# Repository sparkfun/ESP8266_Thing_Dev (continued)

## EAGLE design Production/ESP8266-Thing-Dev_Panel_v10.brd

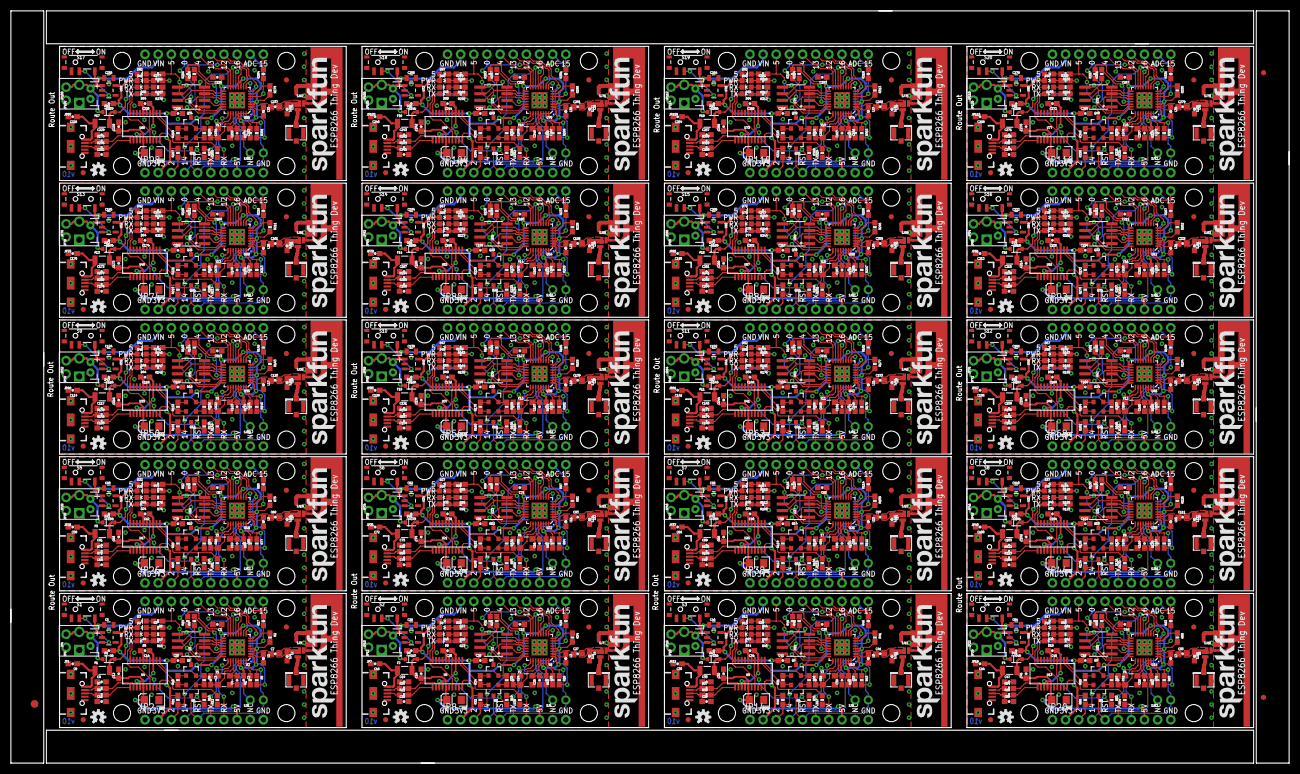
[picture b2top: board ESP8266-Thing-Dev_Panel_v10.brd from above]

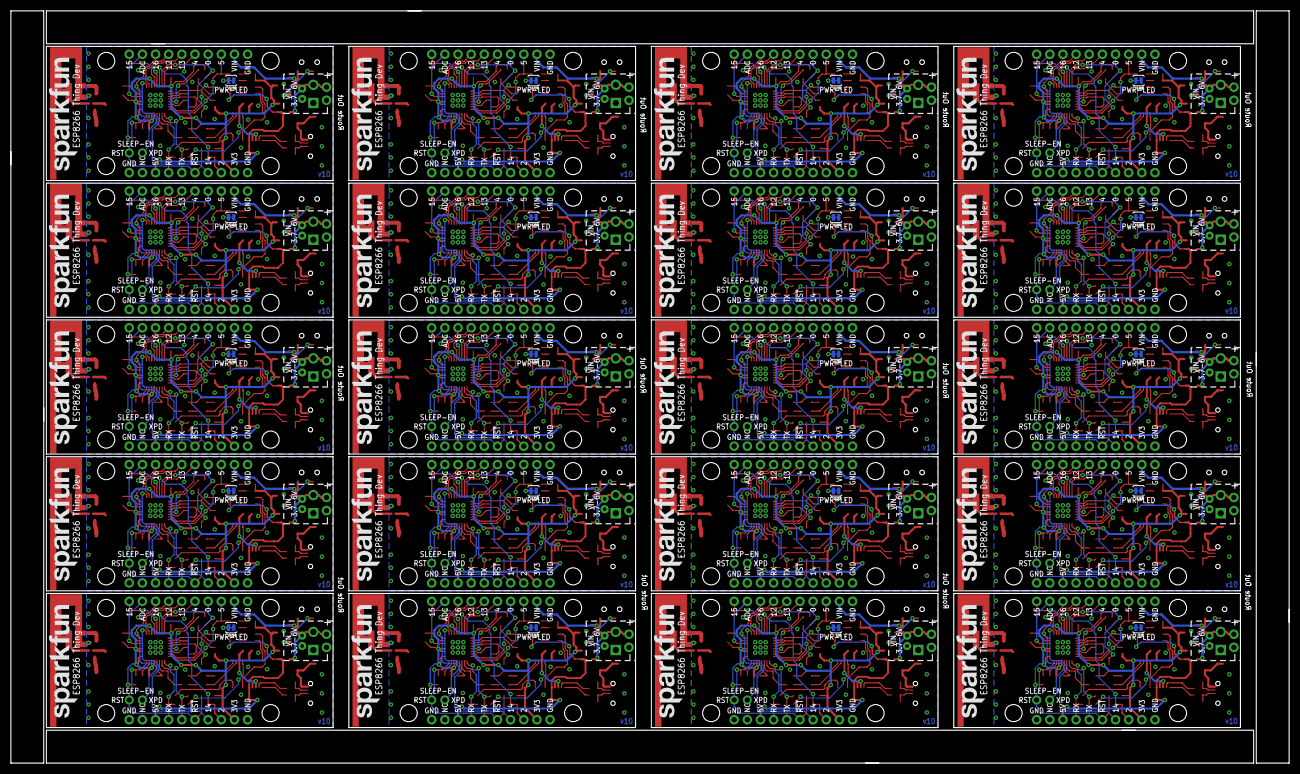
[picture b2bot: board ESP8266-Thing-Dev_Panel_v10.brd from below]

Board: 2 copper layers, 246.9 x 145.3 mm, 1363 parts (40 on the bottom side), 1040 nets.

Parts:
C1, C15, C29, C43, C57, C71, C85, C99, C113, C127, C141, C155, C169, C183, C197, C211, C225, C239, C253, C267: 10uF; 0603-CAP
C2, C8, C10, C12, C14, C16, C18, C20, C23, C28, C30, C32, C34, C37, C42, C44, C46, C48, C51, C56, C58, C60, C62, C65, C70, C72, C74, C76, C79, C84, C86, C88, C90, C93, C98, C100, C102, C104, C107, C112, C114, C116, C118, C121, C126, C128, C130, C132, C135, C140, C142, C144, C146, C149, C154, C156, C158, C160, C163, C168, C170, C172, C174, C177, C182, C184, C186, C188, C191, C196, C198, C200, C202, C205, C210, C212, C214, C216, C219, C224, C226, C228, C230, C233, C238, C240, C242, C244, C247, C252, C254, C256, C258, C261, C266, C268, C270, C272, C275, C280: 0.1uF; 0603-CAP
C3, C4, C24, C25, C38, C39, C52, C53, C66, C67, C80, C81, C94, C95, C108, C109, C122, C123, C136, C137, C150, C151, C164, C165, C178, C179, C192, C193, C206, C207, C220, C221, C234, C235, C248, C249, C262, C263, C276, C277: 10pF; 0603-CAP
C5, C26, C40, C54, C68, C82, C96, C110, C124, C138, C152, C166, C180, C194, C208, C222, C236, C250, C264, C278: 1.0uF; 0805
C6, C17, C31, C45, C59, C73, C87, C101, C115, C129, C143, C157, C171, C185, C199, C213, C227, C241, C255, C269: 2.2uF; 0603-CAP
C7, C27, C41, C55, C69, C83, C97, C111, C125, C139, C153, C167, C181, C195, C209, C223, C237, C251, C265, C279: 5.6pF; 0603-CAP
C9, C11, C19, C22, C33, C36, C47, C50, C61, C64, C75, C78, C89, C92, C103, C106, C117, C120, C131, C134, C145, C148, C159, C162, C173, C176, C187, C190, C201, C204, C215, C218, C229, C232, C243, C246, C257, C260, C271, C274: 47pF; 0603-CAP
C13, C21, C35, C49, C63, C77, C91, C105, C119, C133, C147, C161, C175, C189, C203, C217, C231, C245, C259, C273: 10uF; EIA3216
D1, D8, D13, D18, D23, D28, D33, D38, D43, D48, D53, D58, D63, D68, D73, D78, D83, D88, D93, D98: BAT20J; SOD-323
D2, D6, D11, D16, D21, D26, D31, D36, D41, D46, D51, D56, D61, D66, D71, D76, D81, D86, D91, D96: RED; LED-0603
D3, D7, D12, D17, D22, D27, D32, D37, D42, D47, D52, D57, D62, D67, D72, D77, D82, D87, D92, D97: BLUE; LED-0603
D4, D10, D15, D20, D25, D30, D35, D40, D45, D50, D55, D60, D65, D70, D75, D80, D85, D90, D95, D100: Yellow; LED-0603
D5, D9, D14, D19, D24, D29, D34, D39, D44, D49, D54, D59, D64, D69, D74, D79, D84, D89, D94, D99: GREEN; LED-0603
E1, E2, E3, E4, E5, E6, E7, E8, E9, E10, E11, E12, E13, E14, E15, E16, E17, E18, E19, E20: ANTENNATRACE; TRACE_ANTENNA_2.4GHZ_25.7MM
E$1: FIDUCIAL-1.5X3
E$7, E$8: FIDUCIAL-1X2
F1, F2, F3, F4, F5, F6, F7, F8, F9, F10, F11, F12, F13, F14, F15, F16, F17, F18, F19, F20: 500mA; PTC-1206
FID1, FID2, FID3, FID4, FID5, FID6, FID7, FID8, FID9, FID10, FID11, FID12, FID13, FID14, FID15, FID16, FID17, FID18, FID19, FID20, FID21, FID22, FID23, FID24, FID25, FID26, FID27, FID28, FID29, FID30, FID31, FID32, FID33, FID34, FID35, FID36, FID37, FID38, FID39, FID40: FIDUCIAL1X2; FIDUCIAL-1X2
J1, J2, J3, J4, J5, J6, J7, J8, J9, J10, J11, J12, J13, J14, J15, J16, J17, J18, J19, J20: DNP; U.FL
JP1, JP7, JP13, JP19, JP25, JP31, JP37, JP43, JP49, JP55, JP61, JP67, JP73, JP79, JP85, JP91, JP97, JP103, JP109, JP115: USB-B-MICRO-SMD_V03
JP2, JP3, JP8, JP9, JP14, JP15, JP20, JP21, JP26, JP27, JP32, JP33, JP38, JP39, JP44, JP45, JP50, JP51, JP56, JP57, JP62, JP63, JP68, JP69, JP74, JP75, JP80, JP81, JP86, JP87, JP92, JP93, JP98, JP99, JP104, JP105, JP110, JP111, JP116, JP117: 1X10_NO_SILK
JP4, JP10, JP16, JP22, JP28, JP34, JP40, JP46, JP52, JP58, JP64, JP70, JP76, JP82, JP88, JP94, JP100, JP106, JP112, JP118: JST-2-PTH
JP5, JP11, JP17, JP23, JP29, JP35, JP41, JP47, JP53, JP59, JP65, JP71, JP77, JP83, JP89, JP95, JP101, JP107, JP113, JP119: 1X02_NO_SILK
JP6, JP12, JP18, JP24, JP30, JP36, JP42, JP48, JP54, JP60, JP66, JP72, JP78, JP84, JP90, JP96, JP102, JP108, JP114, JP120: SCREWTERMINAL-3.5MM-2-NS
L1, L2, L3, L4, L5, L6, L7, L8, L9, L10, L11, L12, L13, L14, L15, L16, L17, L18, L19, L20, L21, L22, L23, L24, L25, L26, L27, L28, L29, L30, L31, L32, L33, L34, L35, L36, L37, L38, L39, L40: DNP; 0603
LOGO1, LOGO3, LOGO4, LOGO6, LOGO7, LOGO9, LOGO10, LOGO12, LOGO13, LOGO15, LOGO16, LOGO18, LOGO19, LOGO21, LOGO22, LOGO24, LOGO25, LOGO27, LOGO28, LOGO30, LOGO31, LOGO33, LOGO34, LOGO36, LOGO37, LOGO39, LOGO40, LOGO42, LOGO43, LOGO45, LOGO46, LOGO48, LOGO49, LOGO51, LOGO52, LOGO54, LOGO55, LOGO57, LOGO58, LOGO60: SFE_LOGO_NAME.2_INCH; SFE_LOGO_NAME_.2
LOGO2, LOGO5, LOGO8, LOGO11, LOGO14, LOGO17, LOGO20, LOGO23, LOGO26, LOGO29, LOGO32, LOGO35, LOGO38, LOGO41, LOGO44, LOGO47, LOGO50, LOGO53, LOGO56, LOGO59: OSHW-LOGOS; OSHW-LOGO-S
Q1, Q2, Q3, Q4, Q5, Q6, Q7, Q8, Q9, Q10, Q11, Q12, Q13, Q14, Q15, Q16, Q17, Q18, Q19, Q20, Q21, Q22, Q23, Q24, Q25, Q26, Q27, Q28, Q29, Q30, Q31, Q32, Q33, Q34, Q35, Q36, Q37, Q38, Q39, Q40: MMBT2222A; SOT23-3
R1, R18, R35, R52, R69, R86, R103, R120, R137, R154, R171, R188, R205, R222, R239, R256, R273, R290, R307, R324: 12k; 0603-RES
R2, R5, R9, R10, R11, R14, R17, R24, R26, R29, R31, R32, R33, R34, R41, R43, R46, R48, R49, R50, R51, R58, R60, R63, R65, R66, R67, R68, R75, R77, R80, R82, R83, R84, R85, R92, R94, R97, R99, R100, R101, R102, R109, R111, R114, R116, R117, R118, R119, R126, R128, R131, R133, R134, R135, R136, R143, R145, R148, R150, R151, R152, R153, R160, R162, R165, R167, R168, R169, R170, R177, R179, R182, R184, R185, R186, R187, R194, R196, R199, R201, R202, R203, R204, R211, R213, R216, R218, R219, R220, R221, R228, R230, R233, R235, R236, R237, R238, R245, R247, R250, R252, R253, R254, R255, R262, R264, R267, R269, R270, R271, R272, R279, R281, R284, R286, R287, R288, R289, R296, R298, R301, R303, R304, R305, R306, R313, R315, R318, R320, R321, R322, R323, R330, R332, R335, R337, R338, R339, R340: 10K; 0603-RES
R3, R4, R6, R22, R25, R27, R39, R42, R44, R56, R59, R61, R73, R76, R78, R90, R93, R95, R107, R110, R112, R124, R127, R129, R141, R144, R146, R158, R161, R163, R175, R178, R180, R192, R195, R197, R209, R212, R214, R226, R229, R231, R243, R246, R248, R260, R263, R265, R277, R280, R282, R294, R297, R299, R311, R314, R316, R328, R331, R333: 200; 0603-RES
R7, R8, R20, R21, R37, R38, R54, R55, R71, R72, R88, R89, R105, R106, R122, R123, R139, R140, R156, R157, R173, R174, R190, R191, R207, R208, R224, R225, R241, R242, R258, R259, R275, R276, R292, R293, R309, R310, R326, R327: 27; 0603-RES
R12, R13, R15, R16, R19, R23, R28, R30, R36, R40, R45, R47, R53, R57, R62, R64, R70, R74, R79, R81, R87, R91, R96, R98, R104, R108, R113, R115, R121, R125, R130, R132, R138, R142, R147, R149, R155, R159, R164, R166, R172, R176, R181, R183, R189, R193, R198, R200, R206, R210, R215, R217, R223, R227, R232, R234, R240, R244, R249, R251, R257, R261, R266, R268, R274, R278, R283, R285, R291, R295, R300, R302, R308, R312, R317, R319, R325, R329, R334, R336: 1K; 0603-RES
S1, S2, S3, S4, S5, S6, S7, S8, S9, S10, S11, S12, S13, S14, S15, S16, S17, S18, S19, S20: SWITCH-SPST-SMD-A
SJ1, SJ6, SJ10, SJ14, SJ18, SJ22, SJ26, SJ30, SJ34, SJ38, SJ42, SJ46, SJ50, SJ54, SJ58, SJ62, SJ66, SJ70, SJ74, SJ78: PWRLED; PAD-JUMPER-2-NC_BY_TRACE_YES_SILK
SJ2, SJ5, SJ9, SJ13, SJ17, SJ21, SJ25, SJ29, SJ33, SJ37, SJ41, SJ45, SJ49, SJ53, SJ57, SJ61, SJ65, SJ69, SJ73, SJ77: SLEEP-PTH; PTH-JUMPER-2-NO_NO_SILK
SJ3, SJ7, SJ11, SJ15, SJ19, SJ23, SJ27, SJ31, SJ35, SJ39, SJ43, SJ47, SJ51, SJ55, SJ59, SJ63, SJ67, SJ71, SJ75, SJ79: TRACE; PAD-JUMPER-2-NC_BY_PASTE_NO_SILK
SJ4, SJ8, SJ12, SJ16, SJ20, SJ24, SJ28, SJ32, SJ36, SJ40, SJ44, SJ48, SJ52, SJ56, SJ60, SJ64, SJ68, SJ72, SJ76, SJ80: U.FL; PAD-JUMPER-2-NO_NO_SILK
STANDOFF1, STANDOFF2, STANDOFF3, STANDOFF4, STANDOFF5, STANDOFF6, STANDOFF7, STANDOFF8, STANDOFF9, STANDOFF10, STANDOFF11, STANDOFF12, STANDOFF13, STANDOFF14, STANDOFF15, STANDOFF16, STANDOFF17, STANDOFF18, STANDOFF19, STANDOFF20, STANDOFF21, STANDOFF22, STANDOFF23, STANDOFF24, STANDOFF25, STANDOFF26, STANDOFF27, STANDOFF28, STANDOFF29, STANDOFF30, STANDOFF31, STANDOFF32, STANDOFF33, STANDOFF34, STANDOFF35, STANDOFF36, STANDOFF37, STANDOFF38, STANDOFF39, STANDOFF40, STANDOFF41, STANDOFF42, STANDOFF43, STANDOFF44, STANDOFF45, STANDOFF46, STANDOFF47, STANDOFF48, STANDOFF49, STANDOFF50, STANDOFF51, STANDOFF52, STANDOFF53, STANDOFF54, STANDOFF55, STANDOFF56, STANDOFF57, STANDOFF58, STANDOFF59, STANDOFF60, STANDOFF61, STANDOFF62, STANDOFF63, STANDOFF64, STANDOFF65, STANDOFF66, STANDOFF67, STANDOFF68, STANDOFF69, STANDOFF70, STANDOFF71, STANDOFF72, STANDOFF73, STANDOFF74, STANDOFF75, STANDOFF76, STANDOFF77, STANDOFF78, STANDOFF79, STANDOFF80: STAND-OFF
U1, U8, U12, U16, U20, U24, U28, U32, U36, U40, U44, U48, U52, U56, U60, U64, U68, U72, U76, U80: AP2112K-3.3V; SOT23-5
U2, U6, U10, U14, U18, U22, U26, U30, U34, U38, U42, U46, U50, U54, U58, U62, U66, U70, U74, U78: ESP8266; QFN32
U3, U7, U11, U15, U19, U23, U27, U31, U35, U39, U43, U47, U51, U55, U59, U63, U67, U71, U75, U79: AT25SF041-SOIC8; SO08
U4, U5, U9, U13, U17, U21, U25, U29, U33, U37, U41, U45, U49, U53, U57, U61, U65, U69, U73, U77: FTS31XS-U; SSOP20_L
Y1, Y2, Y3, Y4, Y5, Y6, Y7, Y8, Y9, Y10, Y11, Y12, Y13, Y14, Y15, Y16, Y17, Y18, Y19, Y20: 26MHz; CRYSTAL-SMD-3.2X2.5

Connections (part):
3.3V_F: C14.1, U4.3, U4.13, U4.14
3.3V_F1: C20.1, U5.3, U5.13, U5.14
3.3V_F2: C34.1, U9.3, U9.13, U9.14
3.3V_F3: C48.1, U13.3, U13.13, U13.14
3.3V_F4: C62.1, U17.3, U17.13, U17.14
3.3V_F5: C76.1, U21.3, U21.13, U21.14
3.3V_F6: C90.1, U25.3, U25.13, U25.14
3.3V_F7: C104.1, U29.3, U29.13, U29.14
3.3V_F8: C118.1, U33.3, U33.13, U33.14
3.3V_F9: C132.1, U37.3, U37.13, U37.14
3.3V_F10: C146.1, U41.3, U41.13, U41.14
3.3V_F11: C160.1, U45.3, U45.13, U45.14
3.3V_F12: C174.1, U49.3, U49.13, U49.14
3.3V_F13: C188.1, U53.3, U53.13, U53.14
3.3V_F14: C202.1, U57.3, U57.13, U57.14
3.3V_F15: C216.1, U61.3, U61.13, U61.14
3.3V_F16: C230.1, U65.3, U65.13, U65.14
3.3V_F17: C244.1, U69.3, U69.13, U69.14
3.3V_F18: C258.1, U73.3, U73.13, U73.14
3.3V_F19: C272.1, U77.3, U77.13, U77.14
ADC: JP3.9, U2.6
ADC1: JP9.9, U6.6
ADC2: JP15.9, U10.6
ADC3: JP21.9, U14.6
ADC4: JP27.9, U18.6
ADC5: JP33.9, U22.6
ADC6: JP39.9, U26.6
ADC7: JP45.9, U30.6
ADC8: JP51.9, U34.6
ADC9: JP57.9, U38.6
ADC10: JP63.9, U42.6
ADC11: JP69.9, U46.6
ADC12: JP75.9, U50.6
ADC13: JP81.9, U54.6
ADC14: JP87.9, U58.6
ADC15: JP93.9, U62.6
ADC16: JP99.9, U66.6
ADC17: JP105.9, U70.6
ADC18: JP111.9, U74.6
ADC19: JP117.9, U78.6
ANT: J1.P$3, SJ4.1
ANT1: J2.P$3, SJ8.1
ANT2: J3.P$3, SJ12.1
ANT3: J4.P$3, SJ16.1
ANT4: J5.P$3, SJ20.1
ANT5: J6.P$3, SJ24.1
ANT6: J7.P$3, SJ28.1
ANT7: J8.P$3, SJ32.1
ANT8: J9.P$3, SJ36.1
ANT9: J10.P$3, SJ40.1
ANT10: J11.P$3, SJ44.1
ANT11: J12.P$3, SJ48.1
ANT12: J13.P$3, SJ52.1
ANT13: J14.P$3, SJ56.1
ANT14: J15.P$3, SJ60.1
ANT15: J16.P$3, SJ64.1
ANT16: J17.P$3, SJ68.1
ANT17: J18.P$3, SJ72.1
ANT18: J19.P$3, SJ76.1
ANT19: J20.P$3, SJ80.1
CHIP_EN: R2.1, U2.7
CHIP_EN1: R24.1, U6.7
CHIP_EN2: R41.1, U10.7
CHIP_EN3: R58.1, U14.7
CHIP_EN4: R75.1, U18.7
CHIP_EN5: R92.1, U22.7
CHIP_EN6: R109.1, U26.7
CHIP_EN7: R126.1, U30.7
CHIP_EN8: R143.1, U34.7
CHIP_EN9: R160.1, U38.7
CHIP_EN10: R177.1, U42.7
CHIP_EN11: R194.1, U46.7
CHIP_EN12: R211.1, U50.7
CHIP_EN13: R228.1, U54.7
CHIP_EN14: R245.1, U58.7
CHIP_EN15: R262.1, U62.7
CHIP_EN16: R279.1, U66.7
CHIP_EN17: R296.1, U70.7
CHIP_EN18: R313.1, U74.7
CHIP_EN19: R330.1, U78.7
D+: C11.1, JP1.D+1, R8.1
D+1: C22.1, JP7.D+1, R21.1
D+2: C36.1, JP13.D+1, R38.1
D+3: C50.1, JP19.D+1, R55.1
D+4: C64.1, JP25.D+1, R72.1
D+5: C78.1, JP31.D+1, R89.1
D+6: C92.1, JP37.D+1, R106.1
D+7: C106.1, JP43.D+1, R123.1
D+8: C120.1, JP49.D+1, R140.1
D+9: C134.1, JP55.D+1, R157.1
D+10: C148.1, JP61.D+1, R174.1
D+11: C162.1, JP67.D+1, R191.1
D+12: C176.1, JP73.D+1, R208.1
D+13: C190.1, JP79.D+1, R225.1
D+14: C204.1, JP85.D+1, R242.1
D+15: C218.1, JP91.D+1, R259.1
D+16: C232.1, JP97.D+1, R276.1
D+17: C246.1, JP103.D+1, R293.1
D+18: C260.1, JP109.D+1, R310.1
D+19: C274.1, JP115.D+1, R327.1
D-: C9.1, JP1.D-1, R7.1
D-1: C19.1, JP7.D-1, R20.1
D-2: C33.1, JP13.D-1, R37.1
D-3: C47.1, JP19.D-1, R54.1
D-4: C61.1, JP25.D-1, R71.1
D-5: C75.1, JP31.D-1, R88.1
D-6: C89.1, JP37.D-1, R105.1
D-7: C103.1, JP43.D-1, R122.1
D-8: C117.1, JP49.D-1, R139.1
D-9: C131.1, JP55.D-1, R156.1
D-10: C145.1, JP61.D-1, R173.1
D-11: C159.1, JP67.D-1, R190.1
D-12: C173.1, JP73.D-1, R207.1
D-13: C187.1, JP79.D-1, R224.1
D-14: C201.1, JP85.D-1, R241.1
D-15: C215.1, JP91.D-1, R258.1
D-16: C229.1, JP97.D-1, R275.1
D-17: C243.1, JP103.D-1, R292.1
D-18: C257.1, JP109.D-1, R309.1
D-19: C271.1, JP115.D-1, R326.1
DTR: Q2.2, R9.1, U4.1
DTR1: Q4.2, R33.1, U5.1
DTR2: Q6.2, R50.1, U9.1
DTR3: Q8.2, R67.1, U13.1
DTR4: Q10.2, R84.1, U17.1
DTR5: Q12.2, R101.1, U21.1
DTR6: Q14.2, R118.1, U25.1
DTR7: Q16.2, R135.1, U29.1
DTR8: Q18.2, R152.1, U33.1
DTR9: Q20.2, R169.1, U37.1
DTR10: Q22.2, R186.1, U41.1
DTR11: Q24.2, R203.1, U45.1
DTR12: Q26.2, R220.1, U49.1
DTR13: Q28.2, R237.1, U53.1
DTR14: Q30.2, R254.1, U57.1
DTR15: Q32.2, R271.1, U61.1
DTR16: Q34.2, R288.1, U65.1
DTR17: Q36.2, R305.1, U69.1
DTR18: Q38.2, R322.1, U73.1
DTR19: Q40.2, R339.1, U77.1
GND: C1.2, C2.2, C3.1, C4.1, C5.2, C6.2, C8.2, C9.2, C10.2, C11.2, C12.2, C13.C, C14.2, E1.GND, E1.GND2, J1.P$1, J1.P$2, JP1.GND1, JP1.SHIELD1, JP1.SHIELD2, JP1.SHIELD3, JP2.1, JP2.10, JP3.1, JP4.1, JP5.1, JP6.1, L1.2, L2.2, R1.1, R17.1, S1.1, SJ1.1, U1.2, U2.EP, U3.4, U4.6, U4.16, Y1.2, Y1.4
GND1: C15.2, C16.2, C17.2, C18.2, C19.2, C20.2, C21.C, C22.2, C23.2, C24.1, C25.1, C26.2, C28.2, E2.GND, E2.GND2, J2.P$1, J2.P$2, JP7.GND1, JP7.SHIELD1, JP7.SHIELD2, JP7.SHIELD3, JP8.1, JP8.10, JP9.1, JP10.1, JP11.1, JP12.1, L3.2, L4.2, R18.1, R29.1, S2.1, SJ6.1, U5.6, U5.16, U6.EP, U7.4, U8.2, Y2.2, Y2.4
GND2: C29.2, C30.2, C31.2, C32.2, C33.2, C34.2, C35.C, C36.2, C37.2, C38.1, C39.1, C40.2, C42.2, E3.GND, E3.GND2, J3.P$1, J3.P$2, JP13.GND1, JP13.SHIELD1, JP13.SHIELD2, JP13.SHIELD3, JP14.1, JP14.10, JP15.1, JP16.1, JP17.1, JP18.1, L5.2, L6.2, R35.1, R46.1, S3.1, SJ10.1, U9.6, U9.16, U10.EP, U11.4, U12.2, Y3.2, Y3.4
GND3: C43.2, C44.2, C45.2, C46.2, C47.2, C48.2, C49.C, C50.2, C51.2, C52.1, C53.1, C54.2, C56.2, E4.GND, E4.GND2, J4.P$1, J4.P$2, JP19.GND1, JP19.SHIELD1, JP19.SHIELD2, JP19.SHIELD3, JP20.1, JP20.10, JP21.1, JP22.1, JP23.1, JP24.1, L7.2, L8.2, R52.1, R63.1, S4.1, SJ14.1, U13.6, U13.16, U14.EP, U15.4, U16.2, Y4.2, Y4.4
GND4: C57.2, C58.2, C59.2, C60.2, C61.2, C62.2, C63.C, C64.2, C65.2, C66.1, C67.1, C68.2, C70.2, E5.GND, E5.GND2, J5.P$1, J5.P$2, JP25.GND1, JP25.SHIELD1, JP25.SHIELD2, JP25.SHIELD3, JP26.1, JP26.10, JP27.1, JP28.1, JP29.1, JP30.1, L9.2, L10.2, R69.1, R80.1, S5.1, SJ18.1, U17.6, U17.16, U18.EP, U19.4, U20.2, Y5.2, Y5.4
GND5: C71.2, C72.2, C73.2, C74.2, C75.2, C76.2, C77.C, C78.2, C79.2, C80.1, C81.1, C82.2, C84.2, E6.GND, E6.GND2, J6.P$1, J6.P$2, JP31.GND1, JP31.SHIELD1, JP31.SHIELD2, JP31.SHIELD3, JP32.1, JP32.10, JP33.1, JP34.1, JP35.1, JP36.1, L11.2, L12.2, R86.1, R97.1, S6.1, SJ22.1, U21.6, U21.16, U22.EP, U23.4, U24.2, Y6.2, Y6.4
GND6: C85.2, C86.2, C87.2, C88.2, C89.2, C90.2, C91.C, C92.2, C93.2, C94.1, C95.1, C96.2, C98.2, E7.GND, E7.GND2, J7.P$1, J7.P$2, JP37.GND1, JP37.SHIELD1, JP37.SHIELD2, JP37.SHIELD3, JP38.1, JP38.10, JP39.1, JP40.1, JP41.1, JP42.1, L13.2, L14.2, R103.1, R114.1, S7.1, SJ26.1, U25.6, U25.16, U26.EP, U27.4, U28.2, Y7.2, Y7.4
GND7: C99.2, C100.2, C101.2, C102.2, C103.2, C104.2, C105.C, C106.2, C107.2, C108.1, C109.1, C110.2, C112.2, E8.GND, E8.GND2, J8.P$1, J8.P$2, JP43.GND1, JP43.SHIELD1, JP43.SHIELD2, JP43.SHIELD3, JP44.1, JP44.10, JP45.1, JP46.1, JP47.1, JP48.1, L15.2, L16.2, R120.1, R131.1, S8.1, SJ30.1, U29.6, U29.16, U30.EP, U31.4, U32.2, Y8.2, Y8.4
GND8: C113.2, C114.2, C115.2, C116.2, C117.2, C118.2, C119.C, C120.2, C121.2, C122.1, C123.1, C124.2, C126.2, E9.GND, E9.GND2, J9.P$1, J9.P$2, JP49.GND1, JP49.SHIELD1, JP49.SHIELD2, JP49.SHIELD3, JP50.1, JP50.10, JP51.1, JP52.1, JP53.1, JP54.1, L17.2, L18.2, R137.1, R148.1, S9.1, SJ34.1, U33.6, U33.16, U34.EP, U35.4, U36.2, Y9.2, Y9.4
GND9: C127.2, C128.2, C129.2, C130.2, C131.2, C132.2, C133.C, C134.2, C135.2, C136.1, C137.1, C138.2, C140.2, E10.GND, E10.GND2, J10.P$1, J10.P$2, JP55.GND1, JP55.SHIELD1, JP55.SHIELD2, JP55.SHIELD3, JP56.1, JP56.10, JP57.1, JP58.1, JP59.1, JP60.1, L19.2, L20.2, R154.1, R165.1, S10.1, SJ38.1, U37.6, U37.16, U38.EP, U39.4, U40.2, Y10.2, Y10.4
GND10: C141.2, C142.2, C143.2, C144.2, C145.2, C146.2, C147.C, C148.2, C149.2, C150.1, C151.1, C152.2, C154.2, E11.GND, E11.GND2, J11.P$1, J11.P$2, JP61.GND1, JP61.SHIELD1, JP61.SHIELD2, JP61.SHIELD3, JP62.1, JP62.10, JP63.1, JP64.1, JP65.1, JP66.1, L21.2, L22.2, R171.1, R182.1, S11.1, SJ42.1, U41.6, U41.16, U42.EP, U43.4, U44.2, Y11.2, Y11.4
GND11: C155.2, C156.2, C157.2, C158.2, C159.2, C160.2, C161.C, C162.2, C163.2, C164.1, C165.1, C166.2, C168.2, E12.GND, E12.GND2, J12.P$1, J12.P$2, JP67.GND1, JP67.SHIELD1, JP67.SHIELD2, JP67.SHIELD3, JP68.1, JP68.10, JP69.1, JP70.1, JP71.1, JP72.1, L23.2, L24.2, R188.1, R199.1, S12.1, SJ46.1, U45.6, U45.16, U46.EP, U47.4, U48.2, Y12.2, Y12.4
GND12: C169.2, C170.2, C171.2, C172.2, C173.2, C174.2, C175.C, C176.2, C177.2, C178.1, C179.1, C180.2, C182.2, E13.GND, E13.GND2, J13.P$1, J13.P$2, JP73.GND1, JP73.SHIELD1, JP73.SHIELD2, JP73.SHIELD3, JP74.1, JP74.10, JP75.1, JP76.1, JP77.1, JP78.1, L25.2, L26.2, R205.1, R216.1, S13.1, SJ50.1, U49.6, U49.16, U50.EP, U51.4, U52.2, Y13.2, Y13.4
GND13: C183.2, C184.2, C185.2, C186.2, C187.2, C188.2, C189.C, C190.2, C191.2, C192.1, C193.1, C194.2, C196.2, E14.GND, E14.GND2, J14.P$1, J14.P$2, JP79.GND1, JP79.SHIELD1, JP79.SHIELD2, JP79.SHIELD3, JP80.1, JP80.10, JP81.1, JP82.1, JP83.1, JP84.1, L27.2, L28.2, R222.1, R233.1, S14.1, SJ54.1, U53.6, U53.16, U54.EP, U55.4, U56.2, Y14.2, Y14.4
GND14: C197.2, C198.2, C199.2, C200.2, C201.2, C202.2, C203.C, C204.2, C205.2, C206.1, C207.1, C208.2, C210.2, E15.GND, E15.GND2, J15.P$1, J15.P$2, JP85.GND1, JP85.SHIELD1, JP85.SHIELD2, JP85.SHIELD3, JP86.1, JP86.10, JP87.1, JP88.1, JP89.1, JP90.1, L29.2, L30.2, R239.1, R250.1, S15.1, SJ58.1, U57.6, U57.16, U58.EP, U59.4, U60.2, Y15.2, Y15.4
GND15: C211.2, C212.2, C213.2, C214.2, C215.2, C216.2, C217.C, C218.2, C219.2, C220.1, C221.1, C222.2, C224.2, E16.GND, E16.GND2, J16.P$1, J16.P$2, JP91.GND1, JP91.SHIELD1, JP91.SHIELD2, JP91.SHIELD3, JP92.1, JP92.10, JP93.1, JP94.1, JP95.1, JP96.1, L31.2, L32.2, R256.1, R267.1, S16.1, SJ62.1, U61.6, U61.16, U62.EP, U63.4, U64.2, Y16.2, Y16.4
GND16: C225.2, C226.2, C227.2, C228.2, C229.2, C230.2, C231.C, C232.2, C233.2, C234.1, C235.1, C236.2, C238.2, E17.GND, E17.GND2, J17.P$1, J17.P$2, JP97.GND1, JP97.SHIELD1, JP97.SHIELD2, JP97.SHIELD3, JP98.1, JP98.10, JP99.1, JP100.1, JP101.1, JP102.1, L33.2, L34.2, R273.1, R284.1, S17.1, SJ66.1, U65.6, U65.16, U66.EP, U67.4, U68.2, Y17.2, Y17.4
GND17: C239.2, C240.2, C241.2, C242.2, C243.2, C244.2, C245.C, C246.2, C247.2, C248.1, C249.1, C250.2, C252.2, E18.GND, E18.GND2, J18.P$1, J18.P$2, JP103.GND1, JP103.SHIELD1, JP103.SHIELD2, JP103.SHIELD3, JP104.1, JP104.10, JP105.1, JP106.1, JP107.1, JP108.1, L35.2, L36.2, R290.1, R301.1, S18.1, SJ70.1, U69.6, U69.16, U70.EP, U71.4, U72.2, Y18.2, Y18.4
GND18: C253.2, C254.2, C255.2, C256.2, C257.2, C258.2, C259.C, C260.2, C261.2, C262.1, C263.1, C264.2, C266.2, E19.GND, E19.GND2, J19.P$1, J19.P$2, JP109.GND1, JP109.SHIELD1, JP109.SHIELD2, JP109.SHIELD3, JP110.1, JP110.10, JP111.1, JP112.1, JP113.1, JP114.1, L37.2, L38.2, R307.1, R318.1, S19.1, SJ74.1, U73.6, U73.16, U74.EP, U75.4, U76.2, Y19.2, Y19.4
GND19: C267.2, C268.2, C269.2, C270.2, C271.2, C272.2, C273.C, C274.2, C275.2, C276.1, C277.1, C278.2, C280.2, E20.GND, E20.GND2, J20.P$1, J20.P$2, JP115.GND1, JP115.SHIELD1, JP115.SHIELD2, JP115.SHIELD3, JP116.1, JP116.10, JP117.1, JP118.1, JP119.1, JP120.1, L39.2, L40.2, R324.1, R335.1, S20.1, SJ78.1, U77.6, U77.16, U78.EP, U79.4, U80.2, Y20.2, Y20.4
GPIO0: JP3.4, Q2.3, R14.1, U2.15
GPIO1: JP8.4, U6.9
GPIO2: JP2.3, R11.1, U2.14
GPIO3: JP9.4, Q4.3, R31.1, U6.15
GPIO4: JP3.5, U2.16
GPIO5: JP3.3, R6.1, U2.24
GPIO6: JP9.3, R27.1, U6.24
GPIO7: JP9.5, U6.16
GPIO8: JP9.8, SJ5.1, U6.8
GPIO9: JP9.10, R29.2, U6.13
GPIO10: JP9.6, U6.12
GPIO11: JP9.7, U6.10
GPIO12: JP3.7, U2.10
GPIO13: JP3.6, U2.12
GPIO14: JP2.4, U2.9
GPIO15: JP3.10, R17.2, U2.13
GPIO16: JP3.8, SJ2.1, U2.8
GPIO17: JP8.3, R32.1, U6.14
GPIO18: JP14.4, U10.9
GPIO19: JP15.4, Q6.3, R48.1, U10.15
GPIO20: JP15.3, R44.1, U10.24
GPIO21: JP15.5, U10.16
GPIO22: JP15.8, SJ9.1, U10.8
GPIO23: JP15.10, R46.2, U10.13
GPIO24: JP15.6, U10.12
GPIO25: JP15.7, U10.10
GPIO26: JP14.3, R49.1, U10.14
GPIO27: JP20.4, U14.9
GPIO28: JP21.4, Q8.3, R65.1, U14.15
GPIO29: JP21.3, R61.1, U14.24
GPIO30: JP21.5, U14.16
GPIO31: JP21.8, SJ13.1, U14.8
GPIO32: JP21.10, R63.2, U14.13
GPIO33: JP21.6, U14.12
GPIO34: JP21.7, U14.10
GPIO35: JP20.3, R66.1, U14.14
GPIO36: JP26.4, U18.9
GPIO37: JP27.4, Q10.3, R82.1, U18.15
GPIO38: JP27.3, R78.1, U18.24
GPIO39: JP27.5, U18.16
GPIO40: JP27.8, SJ17.1, U18.8
GPIO41: JP27.10, R80.2, U18.13
GPIO42: JP27.6, U18.12
GPIO43: JP27.7, U18.10
GPIO44: JP26.3, R83.1, U18.14
GPIO45: JP32.4, U22.9
GPIO46: JP33.4, Q12.3, R99.1, U22.15
GPIO47: JP33.3, R95.1, U22.24
GPIO48: JP33.5, U22.16
GPIO49: JP33.8, SJ21.1, U22.8
GPIO50: JP33.10, R97.2, U22.13
GPIO51: JP33.6, U22.12
GPIO52: JP33.7, U22.10
GPIO53: JP32.3, R100.1, U22.14
GPIO54: JP38.4, U26.9
GPIO55: JP39.4, Q14.3, R116.1, U26.15
GPIO56: JP39.3, R112.1, U26.24
GPIO57: JP39.5, U26.16
GPIO58: JP39.8, SJ25.1, U26.8
GPIO59: JP39.10, R114.2, U26.13
GPIO60: JP39.6, U26.12
GPIO61: JP39.7, U26.10
GPIO62: JP38.3, R117.1, U26.14
GPIO63: JP44.4, U30.9
GPIO64: JP45.4, Q16.3, R133.1, U30.15
GPIO65: JP45.3, R129.1, U30.24
GPIO66: JP45.5, U30.16
GPIO67: JP45.8, SJ29.1, U30.8
GPIO68: JP45.10, R131.2, U30.13
GPIO69: JP45.6, U30.12
GPIO70: JP45.7, U30.10
GPIO71: JP44.3, R134.1, U30.14
GPIO72: JP50.4, U34.9
GPIO73: JP51.4, Q18.3, R150.1, U34.15
GPIO74: JP51.3, R146.1, U34.24
GPIO75: JP51.5, U34.16
GPIO76: JP51.8, SJ33.1, U34.8
GPIO77: JP51.10, R148.2, U34.13
GPIO78: JP51.6, U34.12
GPIO79: JP51.7, U34.10
GPIO80: JP50.3, R151.1, U34.14
GPIO81: JP56.4, U38.9
GPIO82: JP57.4, Q20.3, R167.1, U38.15
GPIO83: JP57.3, R163.1, U38.24
GPIO84: JP57.5, U38.16
GPIO85: JP57.8, SJ37.1, U38.8
GPIO86: JP57.10, R165.2, U38.13
GPIO87: JP57.6, U38.12
GPIO88: JP57.7, U38.10
GPIO89: JP56.3, R168.1, U38.14
GPIO90: JP62.4, U42.9
GPIO91: JP63.4, Q22.3, R184.1, U42.15
GPIO92: JP63.3, R180.1, U42.24
GPIO93: JP63.5, U42.16
GPIO94: JP63.8, SJ41.1, U42.8
GPIO95: JP63.10, R182.2, U42.13
GPIO96: JP63.6, U42.12
GPIO97: JP63.7, U42.10
GPIO98: JP62.3, R185.1, U42.14
GPIO99: JP68.4, U46.9
GPIO100: JP69.4, Q24.3, R201.1, U46.15
GPIO101: JP69.3, R197.1, U46.24
GPIO102: JP69.5, U46.16
GPIO103: JP69.8, SJ45.1, U46.8
GPIO104: JP69.10, R199.2, U46.13
GPIO105: JP69.6, U46.12
GPIO106: JP69.7, U46.10
GPIO107: JP68.3, R202.1, U46.14
GPIO108: JP74.4, U50.9
GPIO109: JP75.4, Q26.3, R218.1, U50.15
GPIO110: JP75.3, R214.1, U50.24
GPIO111: JP75.5, U50.16
GPIO112: JP75.8, SJ49.1, U50.8
GPIO113: JP75.10, R216.2, U50.13
GPIO114: JP75.6, U50.12
GPIO115: JP75.7, U50.10
GPIO116: JP74.3, R219.1, U50.14
GPIO117: JP80.4, U54.9
GPIO118: JP81.4, Q28.3, R235.1, U54.15
GPIO119: JP81.3, R231.1, U54.24
GPIO120: JP81.5, U54.16
GPIO121: JP81.8, SJ53.1, U54.8
GPIO122: JP81.10, R233.2, U54.13
GPIO123: JP81.6, U54.12
GPIO124: JP81.7, U54.10
GPIO125: JP80.3, R236.1, U54.14
GPIO126: JP86.4, U58.9
GPIO127: JP87.4, Q30.3, R252.1, U58.15
GPIO128: JP87.3, R248.1, U58.24
GPIO129: JP87.5, U58.16
GPIO130: JP87.8, SJ57.1, U58.8
GPIO131: JP87.10, R250.2, U58.13
GPIO132: JP87.6, U58.12
GPIO133: JP87.7, U58.10
GPIO134: JP86.3, R253.1, U58.14
GPIO135: JP92.4, U62.9
GPIO136: JP93.4, Q32.3, R269.1, U62.15
GPIO137: JP93.3, R265.1, U62.24
GPIO138: JP93.5, U62.16
GPIO139: JP93.8, SJ61.1, U62.8
GPIO140: JP93.10, R267.2, U62.13
GPIO141: JP93.6, U62.12
GPIO142: JP93.7, U62.10
GPIO143: JP92.3, R270.1, U62.14
GPIO144: JP98.4, U66.9
GPIO145: JP99.4, Q34.3, R286.1, U66.15
GPIO146: JP99.3, R282.1, U66.24
GPIO147: JP99.5, U66.16
GPIO148: JP99.8, SJ65.1, U66.8
GPIO149: JP99.10, R284.2, U66.13
GPIO150: JP99.6, U66.12
GPIO151: JP99.7, U66.10
GPIO152: JP98.3, R287.1, U66.14
GPIO153: JP104.4, U70.9
GPIO154: JP105.4, Q36.3, R303.1, U70.15
GPIO155: JP105.3, R299.1, U70.24
GPIO156: JP105.5, U70.16
GPIO157: JP105.8, SJ69.1, U70.8
GPIO158: JP105.10, R301.2, U70.13
GPIO159: JP105.6, U70.12
GPIO160: JP105.7, U70.10
GPIO161: JP104.3, R304.1, U70.14
GPIO162: JP110.4, U74.9
GPIO163: JP111.4, Q38.3, R320.1, U74.15
GPIO164: JP111.3, R316.1, U74.24
GPIO165: JP111.5, U74.16
GPIO166: JP111.8, SJ73.1, U74.8
GPIO167: JP111.10, R318.2, U74.13
GPIO168: JP111.6, U74.12
GPIO169: JP111.7, U74.10
GPIO170: JP110.3, R321.1, U74.14
GPIO171: JP116.4, U78.9
GPIO172: JP117.4, Q40.3, R337.1, U78.15
GPIO173: JP117.3, R333.1, U78.24
GPIO174: JP117.5, U78.16
GPIO175: JP117.8, SJ77.1, U78.8
GPIO176: JP117.10, R335.2, U78.13
GPIO177: JP117.6, U78.12
GPIO178: JP117.7, U78.10
GPIO179: JP116.3, R338.1, U78.14
LNA: C7.1, L1.1, U2.2
LNA1: C27.1, L3.1, U6.2
LNA2: C7.2, L2.1, SJ3.1, SJ4.2
LNA3: C27.2, L4.1, SJ7.1, SJ8.2
LNA4: C41.1, L5.1, U10.2
LNA5: C41.2, L6.1, SJ11.1, SJ12.2
LNA6: C55.1, L7.1, U14.2
LNA7: C55.2, L8.1, SJ15.1, SJ16.2
LNA8: C69.1, L9.1, U18.2
LNA9: C69.2, L10.1, SJ19.1, SJ20.2
LNA10: C83.1, L11.1, U22.2
LNA11: C83.2, L12.1, SJ23.1, SJ24.2
LNA12: C97.1, L13.1, U26.2
LNA13: C97.2, L14.1, SJ27.1, SJ28.2
LNA14: C111.1, L15.1, U30.2
LNA15: C111.2, L16.1, SJ31.1, SJ32.2
LNA16: C125.1, L17.1, U34.2
LNA17: C125.2, L18.1, SJ35.1, SJ36.2
LNA18: C139.1, L19.1, U38.2
LNA19: C139.2, L20.1, SJ39.1, SJ40.2
LNA20: C153.1, L21.1, U42.2
LNA21: C153.2, L22.1, SJ43.1, SJ44.2
LNA22: C167.1, L23.1, U46.2
LNA23: C167.2, L24.1, SJ47.1, SJ48.2
LNA24: C181.1, L25.1, U50.2
LNA25: C181.2, L26.1, SJ51.1, SJ52.2
LNA26: C195.1, L27.1, U54.2
LNA27: C195.2, L28.1, SJ55.1, SJ56.2
LNA28: C209.1, L29.1, U58.2
LNA29: C209.2, L30.1, SJ59.1, SJ60.2
LNA30: C223.1, L31.1, U62.2
LNA31: C223.2, L32.1, SJ63.1, SJ64.2
LNA32: C237.1, L33.1, U66.2
LNA33: C237.2, L34.1, SJ67.1, SJ68.2
LNA34: C251.1, L35.1, U70.2
LNA35: C251.2, L36.1, SJ71.1, SJ72.2
LNA36: C265.1, L37.1, U74.2
LNA37: C265.2, L38.1, SJ75.1, SJ76.2
LNA38: C279.1, L39.1, U78.2
LNA39: C279.2, L40.1, SJ79.1, SJ80.2
unnamed: R1.2, U2.31
unnamed: C4.2, U2.28, Y1.3
unnamed: C3.2, U2.27, Y1.1
unnamed: R7.2, U4.12
unnamed: R3.2, SJ1.2
unnamed: Q1.1, R9.2
unnamed: R8.2, U4.11
unnamed: D5.A, R16.2
unnamed: D3.C, R6.2
unnamed: D4.A, R15.2
unnamed: D2.C, R3.1
unnamed: Q2.1, R10.2
unnamed: R18.2, U6.31
unnamed: S1.2, U1.3
unnamed: C25.2, U6.28, Y2.3
unnamed: C24.2, U6.27, Y2.1
unnamed: D7.C, R27.2
unnamed: D9.A, R23.2
unnamed: D10.A, R28.2
unnamed: R20.2, U5.12
unnamed: R21.2, U5.11
unnamed: D6.C, R22.1
unnamed: S2.2, U8.3
unnamed: R22.2, SJ6.2
unnamed: Q3.1, R33.2
unnamed: Q4.1, R34.2
unnamed: R35.2, U10.31
unnamed: C39.2, U10.28, Y3.3
unnamed: C38.2, U10.27, Y3.1
unnamed: D12.C, R44.2
unnamed: D14.A, R40.2
unnamed: D15.A, R45.2
unnamed: R37.2, U9.12
unnamed: R38.2, U9.11
unnamed: D11.C, R39.1
unnamed: S3.2, U12.3
unnamed: R39.2, SJ10.2
unnamed: Q5.1, R50.2
unnamed: Q6.1, R51.2
unnamed: R52.2, U14.31
unnamed: C53.2, U14.28, Y4.3
unnamed: C52.2, U14.27, Y4.1
unnamed: D17.C, R61.2
unnamed: D19.A, R57.2
unnamed: D20.A, R62.2
unnamed: R54.2, U13.12
unnamed: R55.2, U13.11
unnamed: D16.C, R56.1
unnamed: S4.2, U16.3
unnamed: R56.2, SJ14.2
unnamed: Q7.1, R67.2
unnamed: Q8.1, R68.2
unnamed: R69.2, U18.31
unnamed: C67.2, U18.28, Y5.3
unnamed: C66.2, U18.27, Y5.1
unnamed: D22.C, R78.2
unnamed: D24.A, R74.2
unnamed: D25.A, R79.2
unnamed: R71.2, U17.12
unnamed: R72.2, U17.11
unnamed: D21.C, R73.1
unnamed: S5.2, U20.3
unnamed: R73.2, SJ18.2
unnamed: Q9.1, R84.2
unnamed: Q10.1, R85.2
unnamed: R86.2, U22.31
unnamed: C81.2, U22.28, Y6.3
unnamed: C80.2, U22.27, Y6.1
unnamed: D27.C, R95.2
unnamed: D29.A, R91.2
unnamed: D30.A, R96.2
unnamed: R88.2, U21.12
unnamed: R89.2, U21.11
unnamed: D26.C, R90.1
unnamed: S6.2, U24.3
unnamed: R90.2, SJ22.2
unnamed: Q11.1, R101.2
unnamed: Q12.1, R102.2
unnamed: R103.2, U26.31
unnamed: C95.2, U26.28, Y7.3
unnamed: C94.2, U26.27, Y7.1
unnamed: D32.C, R112.2
unnamed: D34.A, R108.2
unnamed: D35.A, R113.2
unnamed: R105.2, U25.12
unnamed: R106.2, U25.11
unnamed: D31.C, R107.1
unnamed: S7.2, U28.3
unnamed: R107.2, SJ26.2
unnamed: Q13.1, R118.2
unnamed: Q14.1, R119.2
unnamed: R120.2, U30.31
unnamed: C109.2, U30.28, Y8.3
unnamed: C108.2, U30.27, Y8.1
unnamed: D37.C, R129.2
unnamed: D39.A, R125.2
unnamed: D40.A, R130.2
unnamed: R122.2, U29.12
unnamed: R123.2, U29.11
unnamed: D36.C, R124.1
unnamed: S8.2, U32.3
unnamed: R124.2, SJ30.2
unnamed: Q15.1, R135.2
unnamed: Q16.1, R136.2
unnamed: R137.2, U34.31
unnamed: C123.2, U34.28, Y9.3
unnamed: C122.2, U34.27, Y9.1
unnamed: D42.C, R146.2
unnamed: D44.A, R142.2
unnamed: D45.A, R147.2
unnamed: R139.2, U33.12
unnamed: R140.2, U33.11
unnamed: D41.C, R141.1
unnamed: S9.2, U36.3
unnamed: R141.2, SJ34.2
unnamed: Q17.1, R152.2
unnamed: Q18.1, R153.2
unnamed: R154.2, U38.31
unnamed: C137.2, U38.28, Y10.3
unnamed: C136.2, U38.27, Y10.1
unnamed: D47.C, R163.2
unnamed: D49.A, R159.2
unnamed: D50.A, R164.2
unnamed: R156.2, U37.12
unnamed: R157.2, U37.11
unnamed: D46.C, R158.1
unnamed: S10.2, U40.3
unnamed: R158.2, SJ38.2
unnamed: Q19.1, R169.2
unnamed: Q20.1, R170.2
unnamed: R171.2, U42.31
unnamed: C151.2, U42.28, Y11.3
unnamed: C150.2, U42.27, Y11.1
unnamed: D52.C, R180.2
unnamed: D54.A, R176.2
unnamed: D55.A, R181.2
unnamed: R173.2, U41.12
unnamed: R174.2, U41.11
unnamed: D51.C, R175.1
unnamed: S11.2, U44.3
unnamed: R175.2, SJ42.2
unnamed: Q21.1, R186.2
unnamed: Q22.1, R187.2
unnamed: R188.2, U46.31
unnamed: C165.2, U46.28, Y12.3
unnamed: C164.2, U46.27, Y12.1
unnamed: D57.C, R197.2
unnamed: D59.A, R193.2
unnamed: D60.A, R198.2
unnamed: R190.2, U45.12
unnamed: R191.2, U45.11
unnamed: D56.C, R192.1
unnamed: S12.2, U48.3
unnamed: R192.2, SJ46.2
unnamed: Q23.1, R203.2
unnamed: Q24.1, R204.2
unnamed: R205.2, U50.31
unnamed: C179.2, U50.28, Y13.3
unnamed: C178.2, U50.27, Y13.1
unnamed: D62.C, R214.2
unnamed: D64.A, R210.2
unnamed: D65.A, R215.2
unnamed: R207.2, U49.12
unnamed: R208.2, U49.11
unnamed: D61.C, R209.1
unnamed: S13.2, U52.3
unnamed: R209.2, SJ50.2
unnamed: Q25.1, R220.2
unnamed: Q26.1, R221.2
unnamed: R222.2, U54.31
unnamed: C193.2, U54.28, Y14.3
unnamed: C192.2, U54.27, Y14.1
unnamed: D67.C, R231.2
unnamed: D69.A, R227.2
unnamed: D70.A, R232.2
unnamed: R224.2, U53.12
unnamed: R225.2, U53.11
unnamed: D66.C, R226.1
unnamed: S14.2, U56.3
unnamed: R226.2, SJ54.2
unnamed: Q27.1, R237.2
unnamed: Q28.1, R238.2
unnamed: R239.2, U58.31
unnamed: C207.2, U58.28, Y15.3
unnamed: C206.2, U58.27, Y15.1
unnamed: D72.C, R248.2
unnamed: D74.A, R244.2
unnamed: D75.A, R249.2
unnamed: R241.2, U57.12
unnamed: R242.2, U57.11
unnamed: D71.C, R243.1
unnamed: S15.2, U60.3
unnamed: R243.2, SJ58.2
unnamed: Q29.1, R254.2
unnamed: Q30.1, R255.2
unnamed: R256.2, U62.31
unnamed: C221.2, U62.28, Y16.3
unnamed: C220.2, U62.27, Y16.1
unnamed: D77.C, R265.2
unnamed: D79.A, R261.2
unnamed: D80.A, R266.2
unnamed: R258.2, U61.12
unnamed: R259.2, U61.11
unnamed: D76.C, R260.1
unnamed: S16.2, U64.3
unnamed: R260.2, SJ62.2
unnamed: Q31.1, R271.2
unnamed: Q32.1, R272.2
unnamed: R273.2, U66.31
unnamed: C235.2, U66.28, Y17.3
unnamed: C234.2, U66.27, Y17.1
unnamed: D82.C, R282.2
unnamed: D84.A, R278.2
unnamed: D85.A, R283.2
unnamed: R275.2, U65.12
unnamed: R276.2, U65.11
unnamed: D81.C, R277.1
unnamed: S17.2, U68.3
unnamed: R277.2, SJ66.2
unnamed: Q33.1, R288.2
unnamed: Q34.1, R289.2
unnamed: R290.2, U70.31
unnamed: C249.2, U70.28, Y18.3
unnamed: C248.2, U70.27, Y18.1
unnamed: D87.C, R299.2
unnamed: D89.A, R295.2
unnamed: D90.A, R300.2
unnamed: R292.2, U69.12
unnamed: R293.2, U69.11
unnamed: D86.C, R294.1
unnamed: S18.2, U72.3
unnamed: R294.2, SJ70.2
unnamed: Q35.1, R305.2
unnamed: Q36.1, R306.2
unnamed: R307.2, U74.31
unnamed: C263.2, U74.28, Y19.3
unnamed: C262.2, U74.27, Y19.1
unnamed: D92.C, R316.2
unnamed: D94.A, R312.2
unnamed: D95.A, R317.2
unnamed: R309.2, U73.12
unnamed: R310.2, U73.11
unnamed: D91.C, R311.1
unnamed: S19.2, U76.3
unnamed: R311.2, SJ74.2
unnamed: Q37.1, R322.2
unnamed: Q38.1, R323.2
unnamed: R324.2, U78.31
unnamed: C277.2, U78.28, Y20.3
unnamed: C276.2, U78.27, Y20.1
unnamed: D97.C, R333.2
unnamed: D99.A, R329.2
unnamed: D100.A, R334.2
unnamed: R326.2, U77.12
unnamed: R327.2, U77.11
unnamed: D96.C, R328.1
unnamed: S20.2, U80.3
unnamed: R328.2, SJ78.2
unnamed: Q39.1, R339.2
unnamed: Q40.1, R340.2
RESET: JP2.5, Q1.3, R5.1, SJ2.2, U2.32
RESET1: JP8.5, Q3.3, R26.1, SJ5.2, U6.32
RESET2: JP14.5, Q5.3, R43.1, SJ9.2, U10.32
RESET3: JP20.5, Q7.3, R60.1, SJ13.2, U14.32
RESET4: JP26.5, Q9.3, R77.1, SJ17.2, U18.32
RESET5: JP32.5, Q11.3, R94.1, SJ21.2, U22.32
RESET6: JP38.5, Q13.3, R111.1, SJ25.2, U26.32
RESET7: JP44.5, Q15.3, R128.1, SJ29.2, U30.32
RESET8: JP50.5, Q17.3, R145.1, SJ33.2, U34.32
RESET9: JP56.5, Q19.3, R162.1, SJ37.2, U38.32
RESET10: JP62.5, Q21.3, R179.1, SJ41.2, U42.32
RESET11: JP68.5, Q23.3, R196.1, SJ45.2, U46.32
RESET12: JP74.5, Q25.3, R213.1, SJ49.2, U50.32
RESET13: JP80.5, Q27.3, R230.1, SJ53.2, U54.32
RESET14: JP86.5, Q29.3, R247.1, SJ57.2, U58.32
RESET15: JP92.5, Q31.3, R264.1, SJ61.2, U62.32
RESET16: JP98.5, Q33.3, R281.1, SJ65.2, U66.32
RESET17: JP104.5, Q35.3, R298.1, SJ69.2, U70.32
RESET18: JP110.5, Q37.3, R315.1, SJ73.2, U74.32
RESET19: JP116.5, Q39.3, R332.1, SJ77.2, U78.32
RTS: Q1.2, R10.1, U4.2
RTS1: Q3.2, R34.1, U5.2
RTS2: Q5.2, R51.1, U9.2
RTS3: Q7.2, R68.1, U13.2
RTS4: Q9.2, R85.1, U17.2
RTS5: Q11.2, R102.1, U21.2
RTS6: Q13.2, R119.1, U25.2
RTS7: Q15.2, R136.1, U29.2
RTS8: Q17.2, R153.1, U33.2
RTS9: Q19.2, R170.1, U37.2
RTS10: Q21.2, R187.1, U41.2
RTS11: Q23.2, R204.1, U45.2
RTS12: Q25.2, R221.1, U49.2
RTS13: Q27.2, R238.1, U53.2
RTS14: Q29.2, R255.1, U57.2
RTS15: Q31.2, R272.1, U61.2
RTS16: Q33.2, R289.1, U65.2
RTS17: Q35.2, R306.1, U69.2
RTS18: Q37.2, R323.1, U73.2
RTS19: Q39.2, R340.1, U77.2
RXD: R13.2, U4.4
RXD1: R19.2, U5.4
RXD2: R36.2, U9.4
RXD3: R53.2, U13.4
RXD4: R70.2, U17.4
RXD5: R87.2, U21.4
RXD6: R104.2, U25.4
RXD7: R121.2, U29.4
RXD8: R138.2, U33.4
RXD9: R155.2, U37.4
RXD10: R172.2, U41.4
RXD11: R189.2, U45.4
RXD12: R206.2, U49.4
RXD13: R223.2, U53.4
RXD14: R240.2, U57.4
RXD15: R257.2, U61.4
RXD16: R274.2, U65.4
RXD17: R291.2, U69.4
RXD18: R308.2, U73.4
RXD19: R325.2, U77.4
RXLED: D4.C, U4.17
RXLED1: D10.C, U5.17
RXLED2: D15.C, U9.17
RXLED3: D20.C, U13.17
RXLED4: D25.C, U17.17
RXLED5: D30.C, U21.17
RXLED6: D35.C, U25.17
RXLED7: D40.C, U29.17
RXLED8: D45.C, U33.17
RXLED9: D50.C, U37.17
RXLED10: D55.C, U41.17
RXLED11: D60.C, U45.17
RXLED12: D65.C, U49.17
RXLED13: D70.C, U53.17
RXLED14: D75.C, U57.17
RXLED15: D80.C, U61.17
RXLED16: D85.C, U65.17
RXLED17: D90.C, U69.17
RXLED18: D95.C, U73.17
RXLED19: D100.C, U77.17
SD_!HD!: U2.18, U3.7
SD_!HD!1: U6.18, U7.7
SD_!HD!2: U10.18, U11.7
SD_!HD!3: U14.18, U15.7
SD_!HD!4: U18.18, U19.7
SD_!HD!5: U22.18, U23.7
SD_!HD!6: U26.18, U27.7
SD_!HD!7: U30.18, U31.7
SD_!HD!8: U34.18, U35.7
SD_!HD!9: U38.18, U39.7
SD_!HD!10: U42.18, U43.7
SD_!HD!11: U46.18, U47.7
SD_!HD!12: U50.18, U51.7
SD_!HD!13: U54.18, U55.7
SD_!HD!14: U58.18, U59.7
SD_!HD!15: U62.18, U63.7
SD_!HD!16: U66.18, U67.7
SD_!HD!17: U70.18, U71.7
SD_!HD!18: U74.18, U75.7
SD_!HD!19: U78.18, U79.7
SD_!WP!: U2.19, U3.3
SD_!WP!1: U6.19, U7.3
SD_!WP!2: U10.19, U11.3
SD_!WP!3: U14.19, U15.3
SD_!WP!4: U18.19, U19.3
SD_!WP!5: U22.19, U23.3
SD_!WP!6: U26.19, U27.3
SD_!WP!7: U30.19, U31.3
SD_!WP!8: U34.19, U35.3
SD_!WP!9: U38.19, U39.3
SD_!WP!10: U42.19, U43.3
SD_!WP!11: U46.19, U47.3
SD_!WP!12: U50.19, U51.3
SD_!WP!13: U54.19, U55.3
SD_!WP!14: U58.19, U59.3
SD_!WP!15: U62.19, U63.3
SD_!WP!16: U66.19, U67.3
SD_!WP!17: U70.19, U71.3
SD_!WP!18: U74.19, U75.3
SD_!WP!19: U78.19, U79.3
SD_CLK: R4.1, U3.6
SD_CLK0: R4.2, U2.21
SD_CLK1: R25.1, U7.6
SD_CLK2: R25.2, U6.21
SD_CLK3: R42.1, U11.6
SD_CLK4: R42.2, U10.21
SD_CLK5: R59.1, U15.6
SD_CLK6: R59.2, U14.21
SD_CLK7: R76.1, U19.6
SD_CLK8: R76.2, U18.21
SD_CLK9: R93.1, U23.6
SD_CLK10: R93.2, U22.21
SD_CLK11: R110.1, U27.6
SD_CLK12: R110.2, U26.21
SD_CLK13: R127.1, U31.6
SD_CLK14: R127.2, U30.21
SD_CLK15: R144.1, U35.6
SD_CLK16: R144.2, U34.21
SD_CLK17: R161.1, U39.6
SD_CLK18: R161.2, U38.21
SD_CLK19: R178.1, U43.6
SD_CLK20: R178.2, U42.21
SD_CLK21: R195.1, U47.6
SD_CLK22: R195.2, U46.21
SD_CLK23: R212.1, U51.6
SD_CLK24: R212.2, U50.21
SD_CLK25: R229.1, U55.6
SD_CLK26: R229.2, U54.21
SD_CLK27: R246.1, U59.6
SD_CLK28: R246.2, U58.21
SD_CLK29: R263.1, U63.6
SD_CLK30: R263.2, U62.21
SD_CLK31: R280.1, U67.6
SD_CLK32: R280.2, U66.21
SD_CLK33: R297.1, U71.6
SD_CLK34: R297.2, U70.21
SD_CLK35: R314.1, U75.6
SD_CLK36: R314.2, U74.21
SD_CLK37: R331.1, U79.6
SD_CLK38: R331.2, U78.21
SD_CS0: U2.20, U3.1
SD_CS1: U6.20, U7.1
SD_CS2: U10.20, U11.1
SD_CS3: U14.20, U15.1
SD_CS4: U18.20, U19.1
SD_CS5: U22.20, U23.1
SD_CS6: U26.20, U27.1
SD_CS7: U30.20, U31.1
SD_CS8: U34.20, U35.1
SD_CS9: U38.20, U39.1
SD_CS10: U42.20, U43.1
SD_CS11: U46.20, U47.1
SD_CS12: U50.20, U51.1
SD_CS13: U54.20, U55.1
SD_CS14: U58.20, U59.1
SD_CS15: U62.20, U63.1
SD_CS16: U66.20, U67.1
SD_CS17: U70.20, U71.1
SD_CS18: U74.20, U75.1
SD_CS19: U78.20, U79.1
SD_SI: U2.23, U3.5
SD_SI1: U6.23, U7.5
SD_SI2: U10.23, U11.5
SD_SI3: U14.23, U15.5
SD_SI4: U18.23, U19.5
SD_SI5: U22.23, U23.5
SD_SI6: U26.23, U27.5
SD_SI7: U30.23, U31.5
SD_SI8: U34.23, U35.5
SD_SI9: U38.23, U39.5
SD_SI10: U42.23, U43.5
SD_SI11: U46.23, U47.5
SD_SI12: U50.23, U51.5
SD_SI13: U54.23, U55.5
SD_SI14: U58.23, U59.5
SD_SI15: U62.23, U63.5
SD_SI16: U66.23, U67.5
SD_SI17: U70.23, U71.5
SD_SI18: U74.23, U75.5
SD_SI19: U78.23, U79.5
SD_SO: U2.22, U3.2
SD_SO1: U6.22, U7.2
SD_SO2: U10.22, U11.2
SD_SO3: U14.22, U15.2
SD_SO4: U18.22, U19.2
SD_SO5: U22.22, U23.2
SD_SO6: U26.22, U27.2
SD_SO7: U30.22, U31.2
SD_SO8: U34.22, U35.2
SD_SO9: U38.22, U39.2
SD_SO10: U42.22, U43.2
SD_SO11: U46.22, U47.2
SD_SO12: U50.22, U51.2
SD_SO13: U54.22, U55.2
SD_SO14: U58.22, U59.2
SD_SO15: U62.22, U63.2
SD_SO16: U66.22, U67.2
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
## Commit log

2015-07-30 Initial commit of hardware.
2015-08-05 Extending dimensions borders past antenna copper.
2015-09-04 Removing SJ3 - SMD sleep jumper
2015-09-14 Adjusting label header silk a bit
2015-09-14 Fixing dimension lines
2015-09-14 Schematic cleanup, tweaking silkscreen
2015-09-15 Last run-through, minor silk adjustments
2015-09-16 Bumping out dimensions to a 0.01in grid.
2015-09-16 moved fiducials inward for better recognition
2015-09-16 created panel v10
2015-11-05 Adding product info to readme.
2015-11-05 Fixing readme typos
